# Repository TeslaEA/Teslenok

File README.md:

<<<<<<< HEAD
# Описание

* Задача: обновить и сильно видоизменить микроник
* Возраст: 8-11лет
* Количество занятий: 19
* Количество тем: 6

В процессе разработки необходимо создать полный курс обучения, продолжительностью 15-20 занятий или 2 - 2,5 месяца \(8 занятий в месяц по 2 астрономических часа\)

В первую очередь необходимо сделать:

1. Принципиальные схемы ко всем занятиям и дополнительным заданиям \(если нужно\)
2. Схемы сборки всех занятий и дополнительных заданий к ним
3. Список всех компонентов, используемых в курсе
4. Протестировать ВСЕ занятия на стабильность работы
5. Написать краткий конспект преподавателя по всем занятиям \(для внутреннего использования\)

Во вторую очередь необходимо сделать:

1. Подготовить и заказать печатные платы для пайки некоторых самых интересных экспериментов \(для того, что бы дети начали паять ДО начала BEAM-роботов и имели уже готовые схемки на руках\)
2. Написать развернутый конспект для преподавателя
3. Написать полный конспект для ученика и его самостоятельной сборки \(отчуждение курса\)

=======
# Тесленок

* Задача: обновить и сильно видоизменить микроник
* Возраст: 8-11лет
* Количество занятий: 19
* Количество тем: 6

В процессе разработки необходимо создать полный курс обучения, продолжительностью 15-20 занятий или 2 - 2,5 месяца \(8 занятий в месяц по 2 астрономических часа\)

В первую очередь необходимо сделать:

1. Принципиальные схемы ко всем занятиям и дополнительным заданиям \(если нужно\)
2. Схемы сборки всех занятий и дополнительных заданий к ним
3. Список всех компонентов, используемых в курсе
4. Протестировать ВСЕ занятия на стабильность работы
5. Написать краткий конспект преподавателя по всем занятиям \(для внутреннего использования\)

Во вторую очередь необходимо сделать:

1. Подготовить и заказать печатные платы для пайки некоторых самых интересных экспериментов \(для того, что бы дети начали паять ДО начала BEAM-роботов и имели уже готовые схемки на руках\)
2. Написать развернутый конспект для преподавателя
3. Написать полный конспект для ученика и его самостоятельной сборки \(отчуждение курса\)

>>>>>>> f7446b91c112eb8323d611109bb8d3803f14afa5

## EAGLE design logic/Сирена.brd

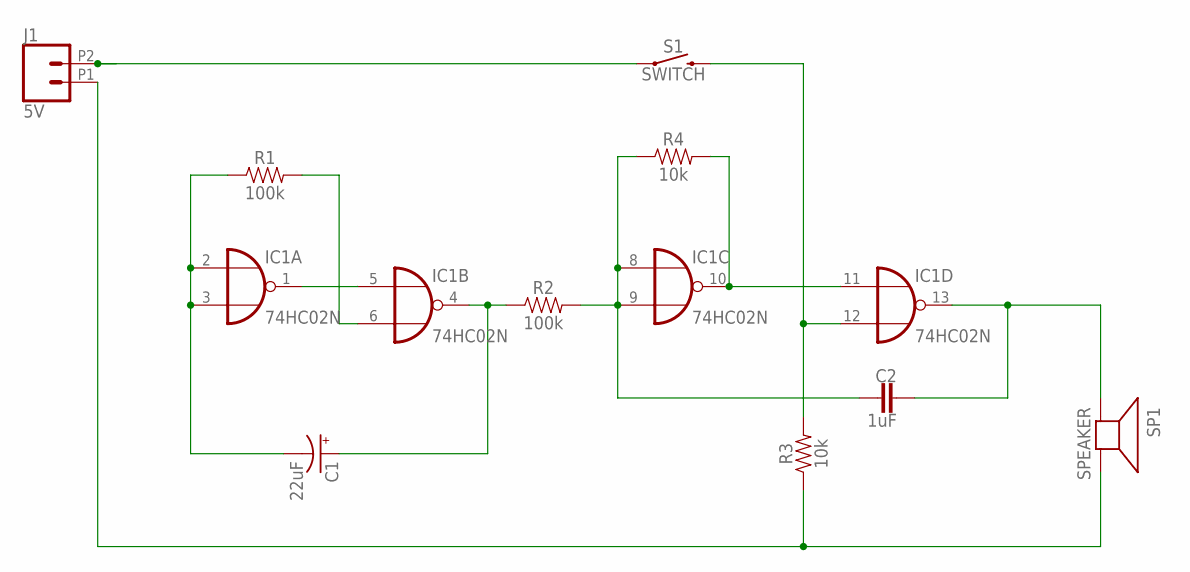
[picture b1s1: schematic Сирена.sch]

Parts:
C1: 22uF; CPOL-RADIAL-2.5MM-5MM
C2: 1uF; CAP-PTH-SMALL-KIT
IC1: 74HC02N; DIL14
J1: 5V; 1X02_2.54_SCREWTERM
R1, R2: 100k; AXIAL-0.3
R3, R4: 10k; AXIAL-0.3
S1: SWITCH; TACTILE_SWITCH_PTH_6.0MM
SP1: SPEAKER; PS12

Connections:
5V: IC1.12 (I1), R3.P$2 (2), S1.3 (2)
GND: IC1.7 (GND), J1.P1 (1), R3.P$1 (1), SP1.P$2 (-)
unnamed: C1.2 (-), IC1.2 (I0), IC1.3 (I1), R1.P$1 (1)
unnamed: IC1.1 (O), IC1.5 (I0)
unnamed: IC1.6 (I1), R1.P$2 (2)
unnamed: C1.1 (+), IC1.4 (O), R2.P$1 (1)
unnamed: C2.2, IC1.8 (I0), IC1.9 (I1), R2.P$2 (2), R4.P$1 (1)
unnamed: IC1.10 (O), IC1.11 (I0), R4.P$2 (2)
unnamed: C2.1, IC1.13 (O), SP1.P$1 (+)
VCC: IC1.14 (VCC), J1.P2 (2), S1.1

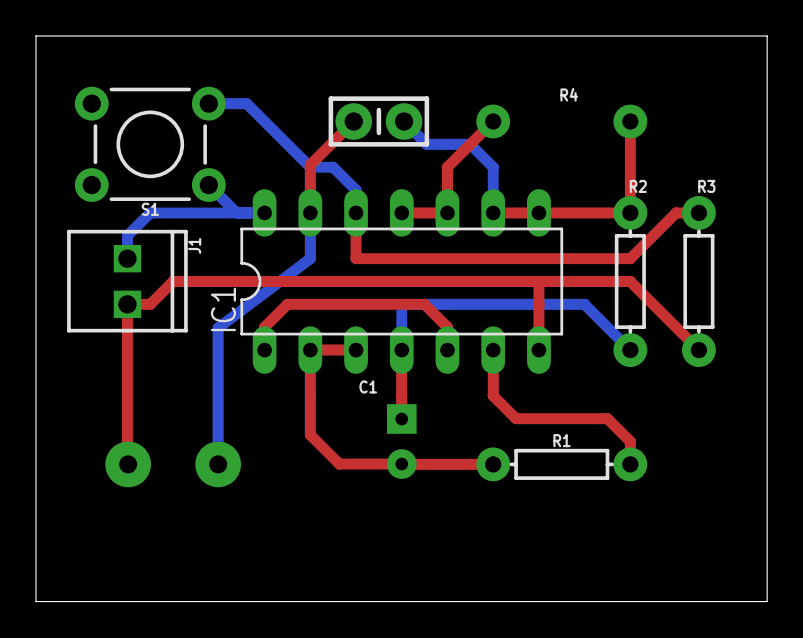
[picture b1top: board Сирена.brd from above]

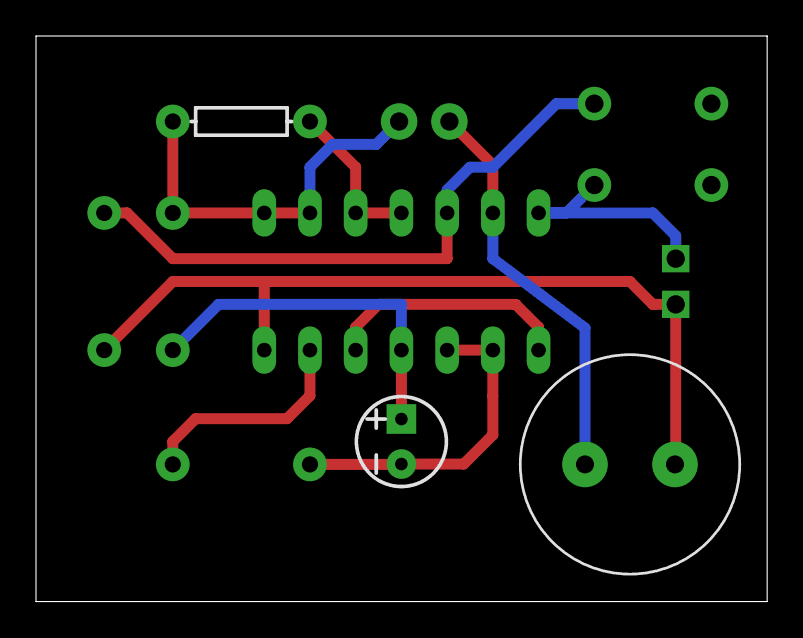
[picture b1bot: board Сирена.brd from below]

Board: 2 copper layers, 40.6 x 31.4 mm, 10 parts (3 on the bottom side), 10 nets.

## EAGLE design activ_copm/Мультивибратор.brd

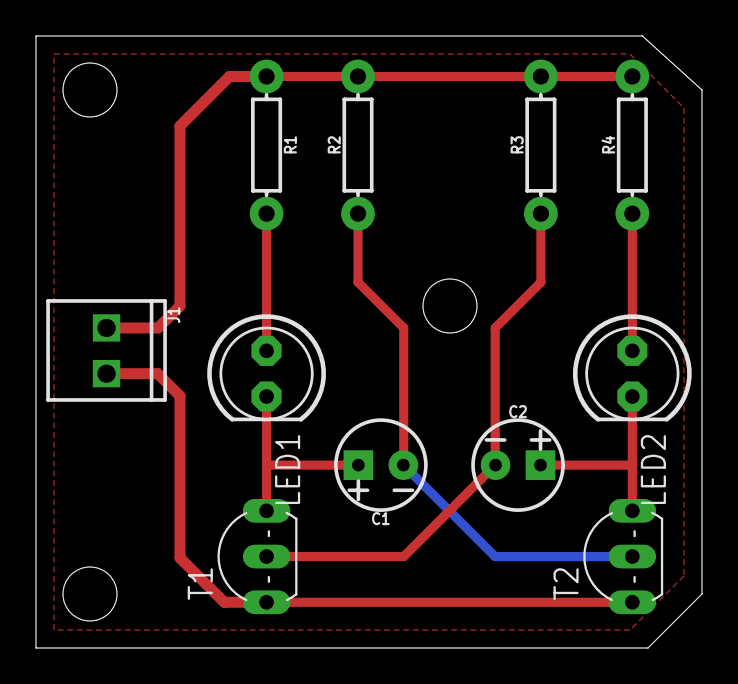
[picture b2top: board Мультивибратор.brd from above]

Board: 2 copper layers, 37.0 x 34.0 mm, 11 parts (0 on the bottom side), 8 nets.

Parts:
C1, C2: 10uF; CPOL-RADIAL-2.5MM-5MM
J1: 1X02_2.54_SCREWTERM
LED1, LED2: LED5MM
R1, R4: 220; AXIAL-0.3
R2, R3: 10k; AXIAL-0.3
T1, T2: 2N2222; TO92-EBC-OVAL

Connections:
+5V: J1.P2, R1.P$1, R2.P$2, R3.P$2, R4.P$2
GND: J1.P1, T1.E, T2.E
unnamed: LED1.A, R1.P$2
unnamed: C1.1, LED1.K, T1.C
unnamed: C2.1, LED2.K, T2.C
unnamed: LED2.A, R4.P$1
unnamed: C1.2, R2.P$1, T2.B
unnamed: C2.2, R3.P$1, T1.B

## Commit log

2019-07-13 Initialize repository
2019-07-13 GitBook: [master] 21 pages and 8 assets modified
2019-07-13 GitBook: [master] 2 pages modified
2019-07-13 GitBook: [master] 4 pages modified
2019-07-13 GitBook: [master] 44 pages modified
2019-07-14 GitBook: [master] 49 pages modified
2019-07-20 GitBook: [master] 23 pages modified
2019-07-20 GitBook: [master] one page modified
2019-07-20 upd
    upd
2019-07-20 GitBook: [master] 2 pages and 9 assets modified
2019-07-20 GitBook: [master] one page and one asset modified
2019-07-20 add
    add
2019-07-20 GitBook: [master] one page and 2 assets modified
2019-07-20 GitBook: [master] one page and 3 assets modified
2019-07-20 GitBook: [master] 2 pages and 2 assets modified
2019-07-20 GitBook: [master] 3 pages and 7 assets modified
2019-07-20 GitBook: [master] 3 pages and 2 assets modified
2019-08-25 GitBook: [master] 3 pages modified
2019-08-25 GitBook: [master] 6 pages modified
2019-08-26 GitBook: [master] 8 pages modified
2019-10-22 GitBook: [master] 29 pages and 3 assets modified
2019-11-08 add mosfet
2020-01-09 add bipolar sch
2020-01-28 add bydil sch
2020-01-30 add bipolar

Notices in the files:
parts and their libraries:
SparkFun-Capacitors: Licensing: Creative Commons ShareAlike 4.0 International - https://creativecommons.org/licenses/by-sa/4.0
